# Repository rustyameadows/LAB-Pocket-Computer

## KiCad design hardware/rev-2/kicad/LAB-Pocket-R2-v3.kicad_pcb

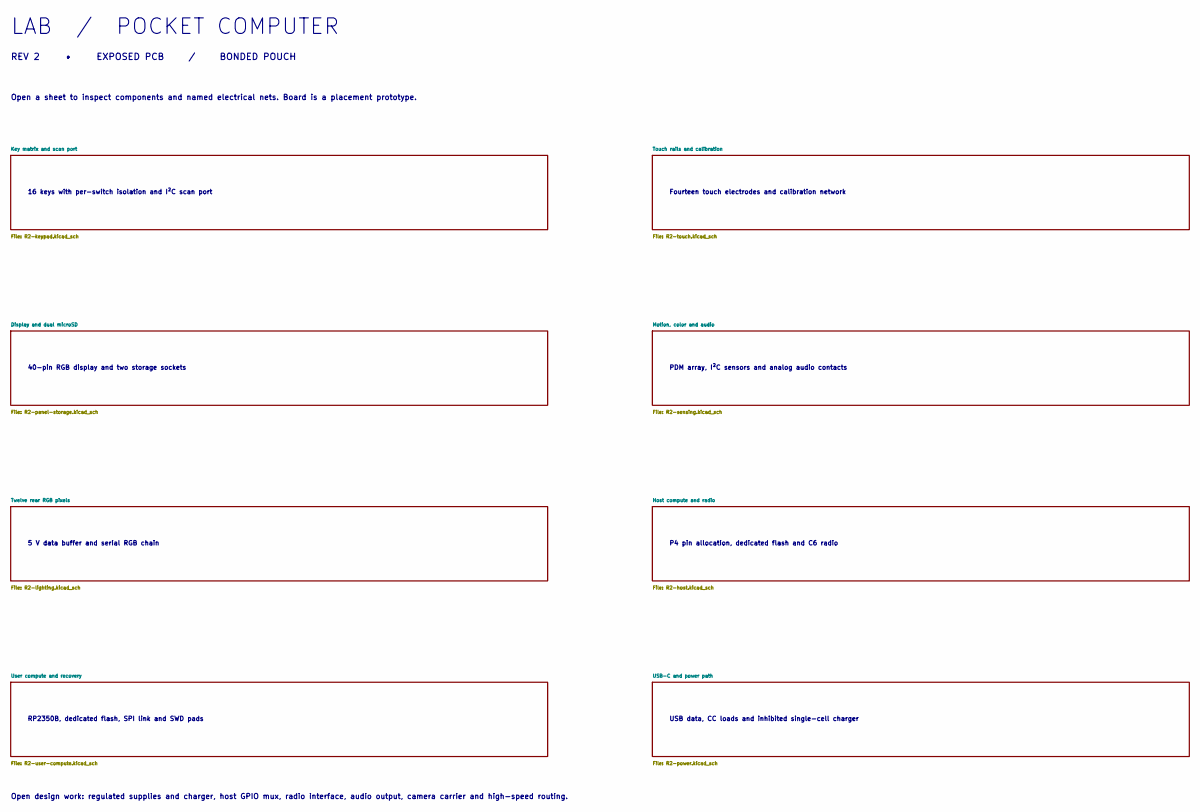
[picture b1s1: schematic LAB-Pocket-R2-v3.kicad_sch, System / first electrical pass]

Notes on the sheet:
LAB / POCKET COMPUTER
REV 2 • EXPOSED PCB / BONDED POUCH
Open a sheet to inspect components and named electrical nets. Board is a placement prototype.
16 keys with per-switch isolation and I²C scan port
Fourteen touch electrodes and calibration network
40-pin RGB display and two storage sockets
PDM array, I²C sensors and analog audio contacts
5 V data buffer and serial RGB chain
P4 pin allocation, dedicated flash and C6 radio
RP2350B, dedicated flash, SPI link and SWD pads
USB data, CC loads and inhibited single-cell charger
Open design work: regulated supplies and charger, host GPIO mux, radio interface, audio output, camera carrier and high-speed routing.

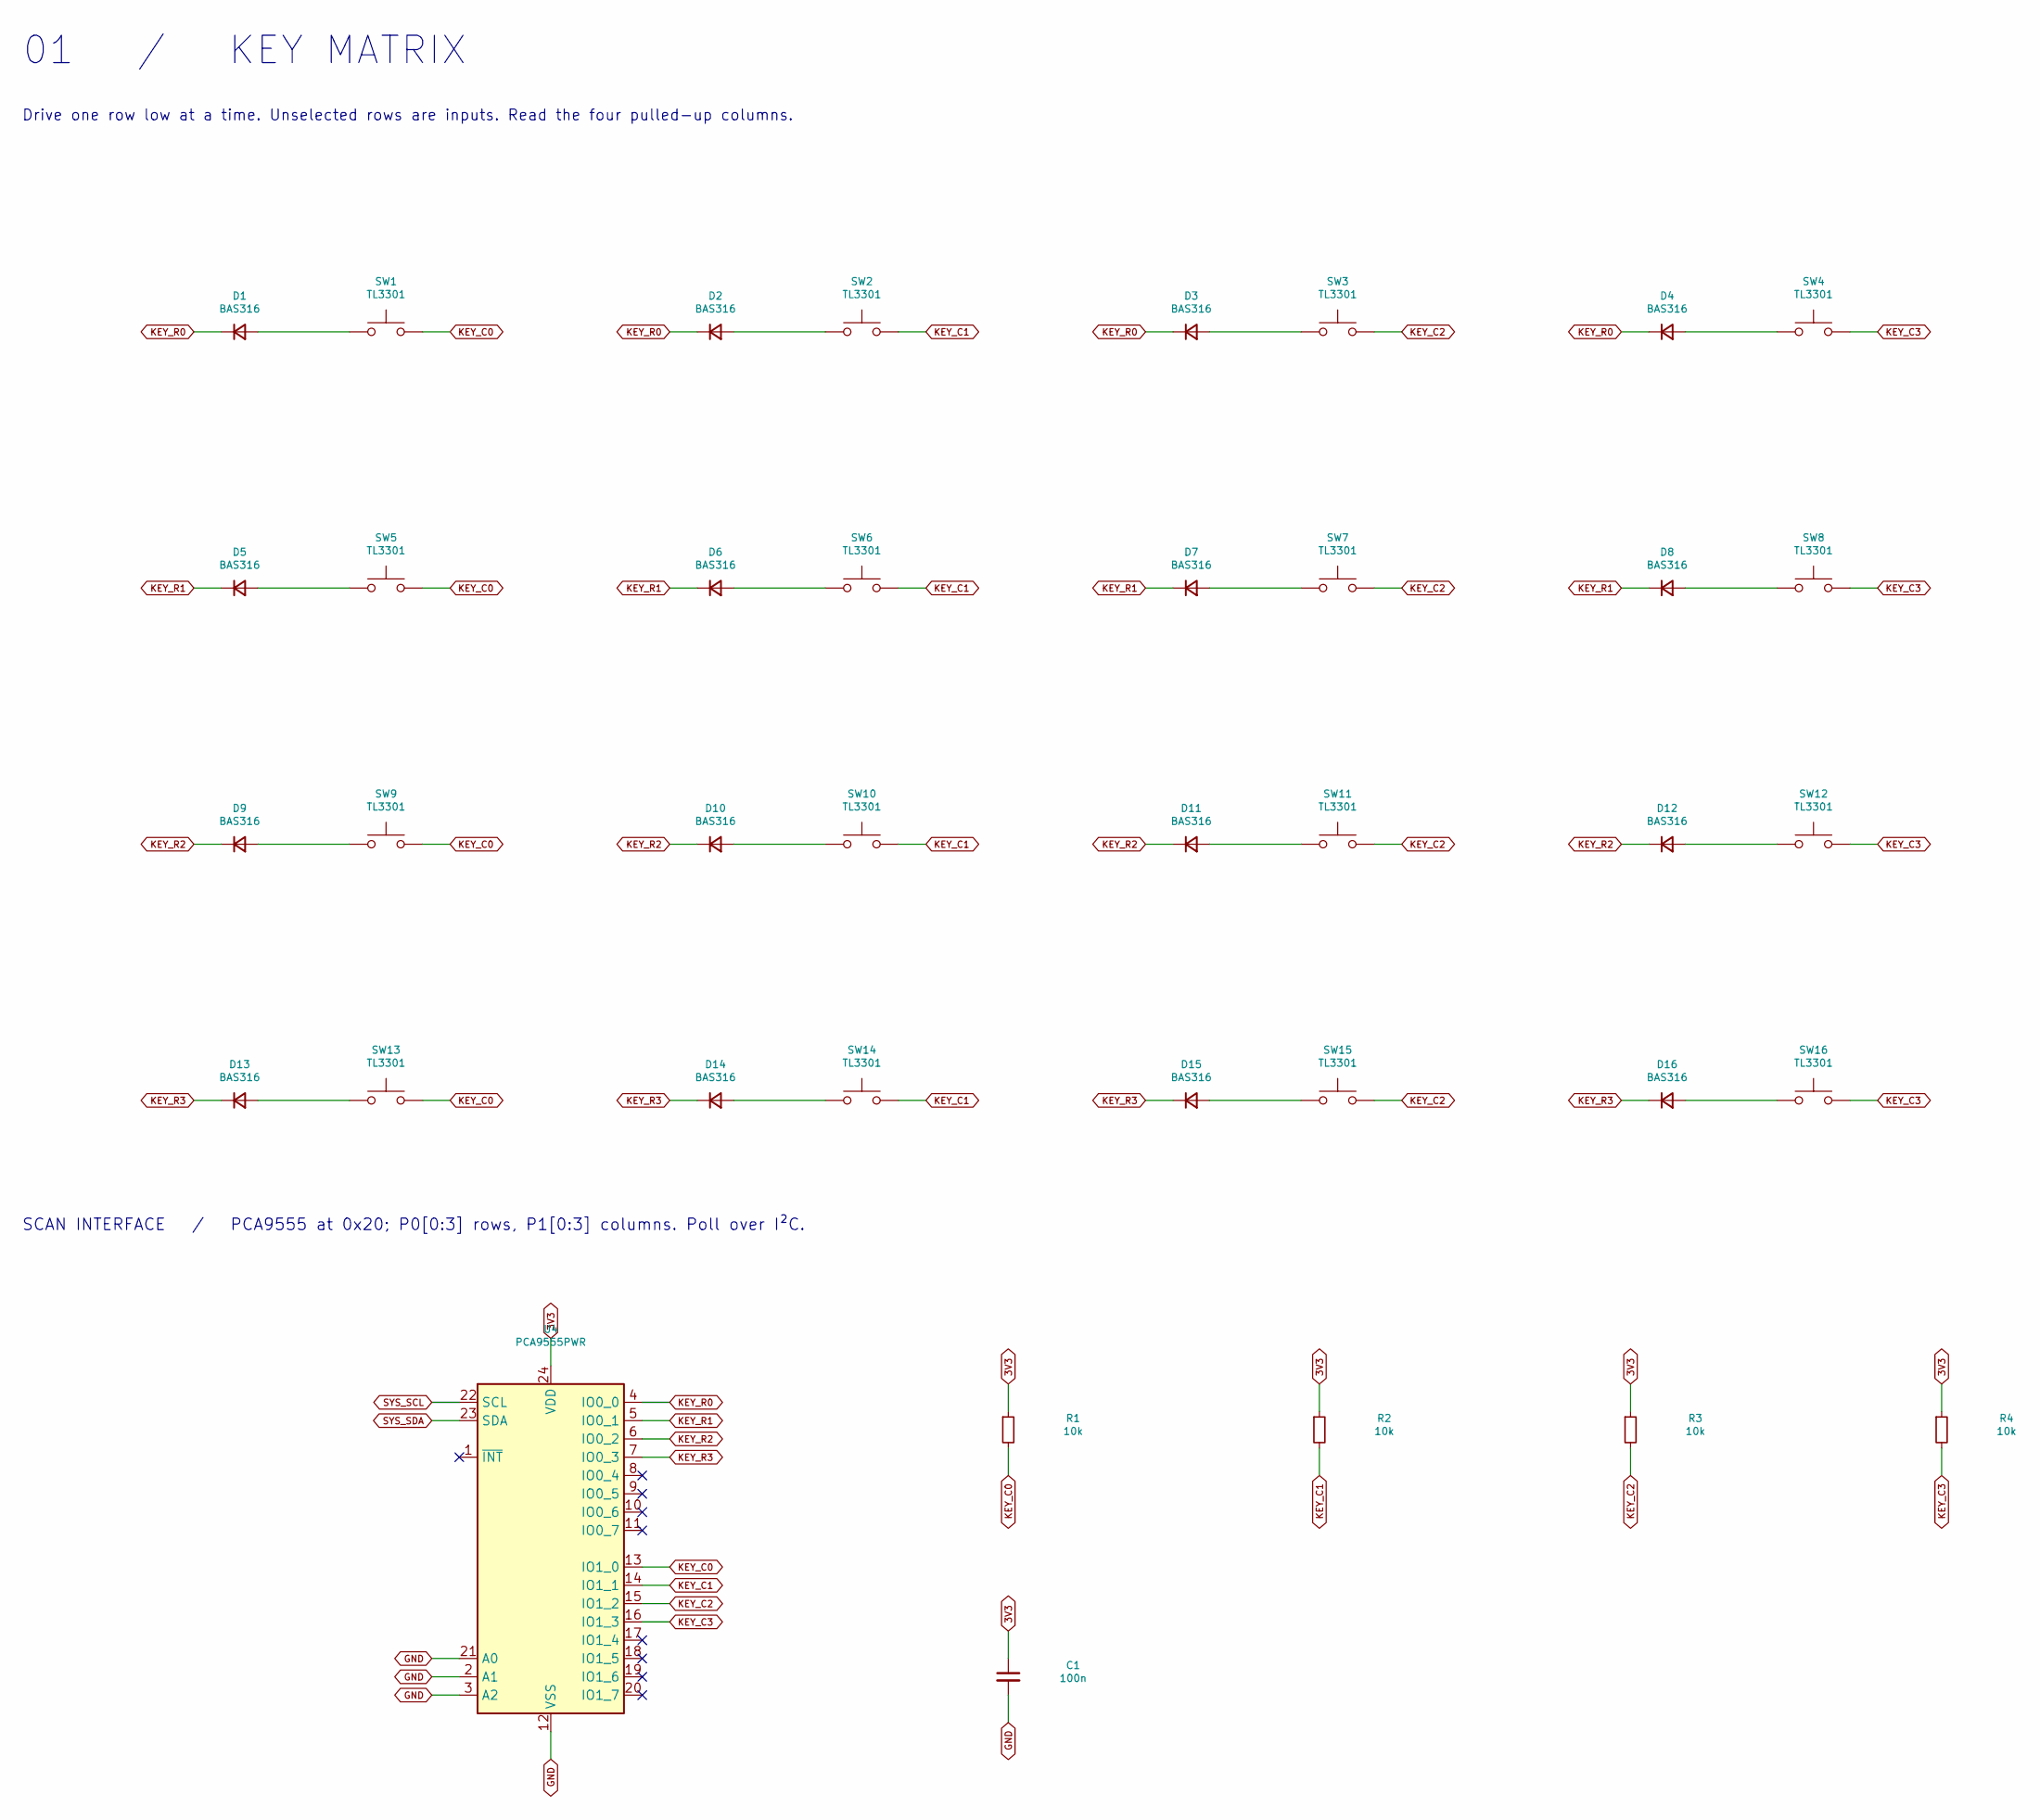
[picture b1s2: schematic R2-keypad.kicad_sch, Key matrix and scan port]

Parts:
C1: 100n; C_0603_1608Metric; MPN C0603C104K5RACTU
D1, D2, D3, D4, D5, D6, D7, D8, D9, D10, D11, D12, D13, D14, D15, D16: BAS316; D_SOD-323; MPN BAS316,115
R1, R2, R3, R4: 10k; R_0603_1608Metric; MPN CRCW060310K0FKEA
SW1, SW2, SW3, SW4, SW5, SW6, SW7, SW8, SW9, SW10, SW11, SW12, SW13, SW14, SW15, SW16: TL3301; SW_Push_1P1T_NO_E-Switch_TL3301NxxxxxG; MPN TL3301NF160QG
U4: PCA9555PWR; TSSOP-24_4.4x7.8mm_P0.65mm; MPN PCA9555PWR

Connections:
3V3: C1.1, R1.1, R2.1, R3.1, R4.1, U4.24 (VDD); also elsewhere on the board
GND: C1.2, U4.2 (A1), U4.3 (A2), U4.12 (VSS), U4.21 (A0); also elsewhere on the board
KEY_C0: R1.2, SW1.2, SW5.2, SW9.2, SW13.2, U4.13 (IO1_0)
KEY_C1: R2.2, SW2.2, SW6.2, SW10.2, SW14.2, U4.14 (IO1_1)
KEY_C2: R3.2, SW3.2, SW7.2, SW11.2, SW15.2, U4.15 (IO1_2)
KEY_C3: R4.2, SW4.2, SW8.2, SW12.2, SW16.2, U4.16 (IO1_3)
KEY_R0: D1.1 (K), D2.1 (K), D3.1 (K), D4.1 (K), U4.4 (IO0_0)
KEY_R1: D5.1 (K), D6.1 (K), D7.1 (K), D8.1 (K), U4.5 (IO0_1)
KEY_R2: D9.1 (K), D10.1 (K), D11.1 (K), D12.1 (K), U4.6 (IO0_2)
KEY_R3: D13.1 (K), D14.1 (K), D15.1 (K), D16.1 (K), U4.7 (IO0_3)
unnamed: D1.2 (A), SW1.1
unnamed: D2.2 (A), SW2.1
unnamed: D3.2 (A), SW3.1
unnamed: D4.2 (A), SW4.1
unnamed: D5.2 (A), SW5.1
unnamed: D6.2 (A), SW6.1
unnamed: D7.2 (A), SW7.1
unnamed: D8.2 (A), SW8.1
unnamed: D9.2 (A), SW9.1
unnamed: D10.2 (A), SW10.1
unnamed: D11.2 (A), SW11.1
unnamed: D12.2 (A), SW12.1
unnamed: D13.2 (A), SW13.1
unnamed: D14.2 (A), SW14.1
unnamed: D15.2 (A), SW15.1
unnamed: D16.2 (A), SW16.1
SYS_SCL: U4.22 (SCL); also elsewhere on the board
SYS_SDA: U4.23 (SDA); also elsewhere on the board

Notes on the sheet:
01 / KEY MATRIX
Drive one row low at a time. Unselected rows are inputs. Read the four pulled-up columns.
SCAN INTERFACE / PCA9555 at 0x20; P0[0:3] rows, P1[0:3] columns. Poll over I²C.

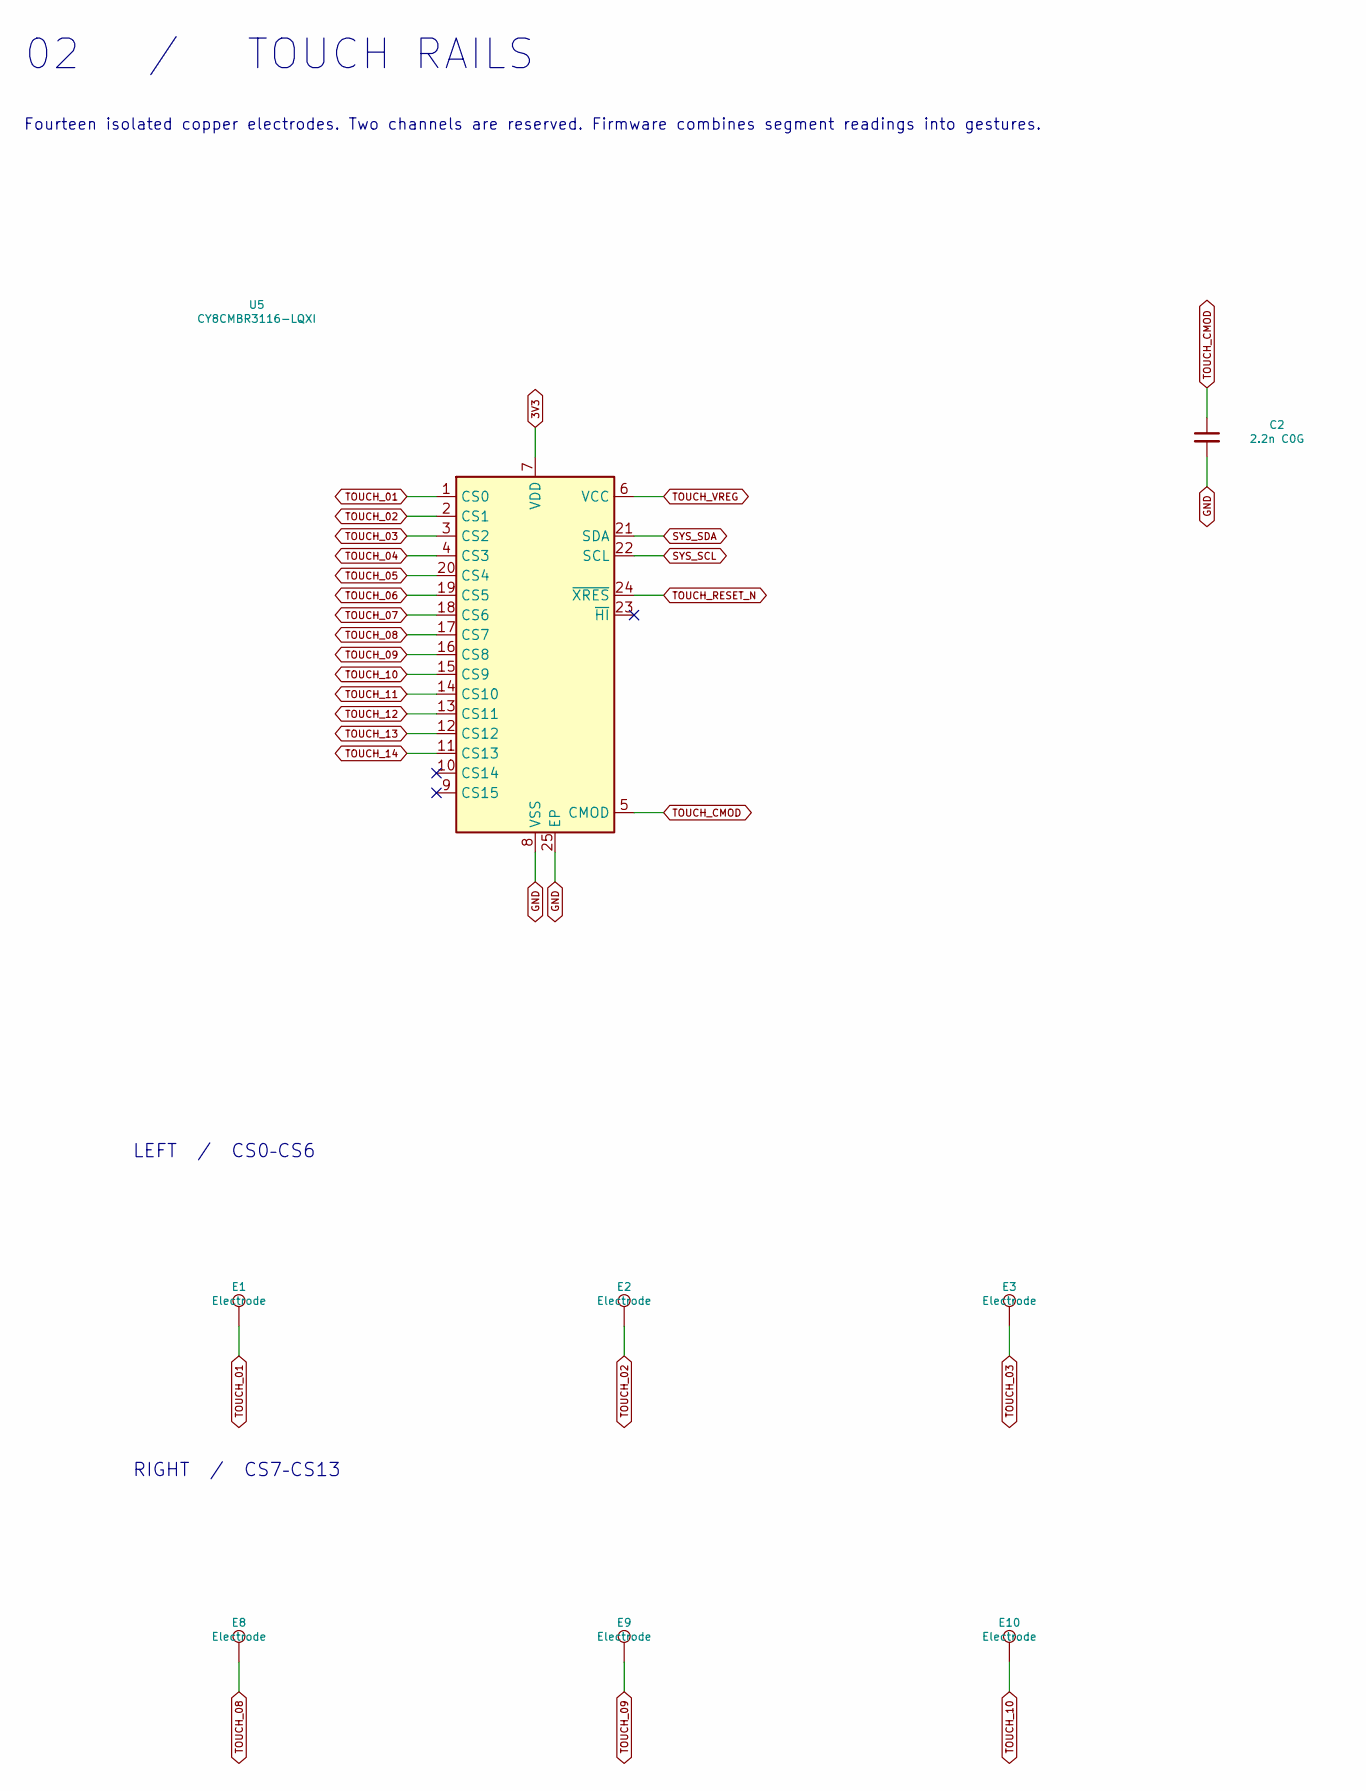
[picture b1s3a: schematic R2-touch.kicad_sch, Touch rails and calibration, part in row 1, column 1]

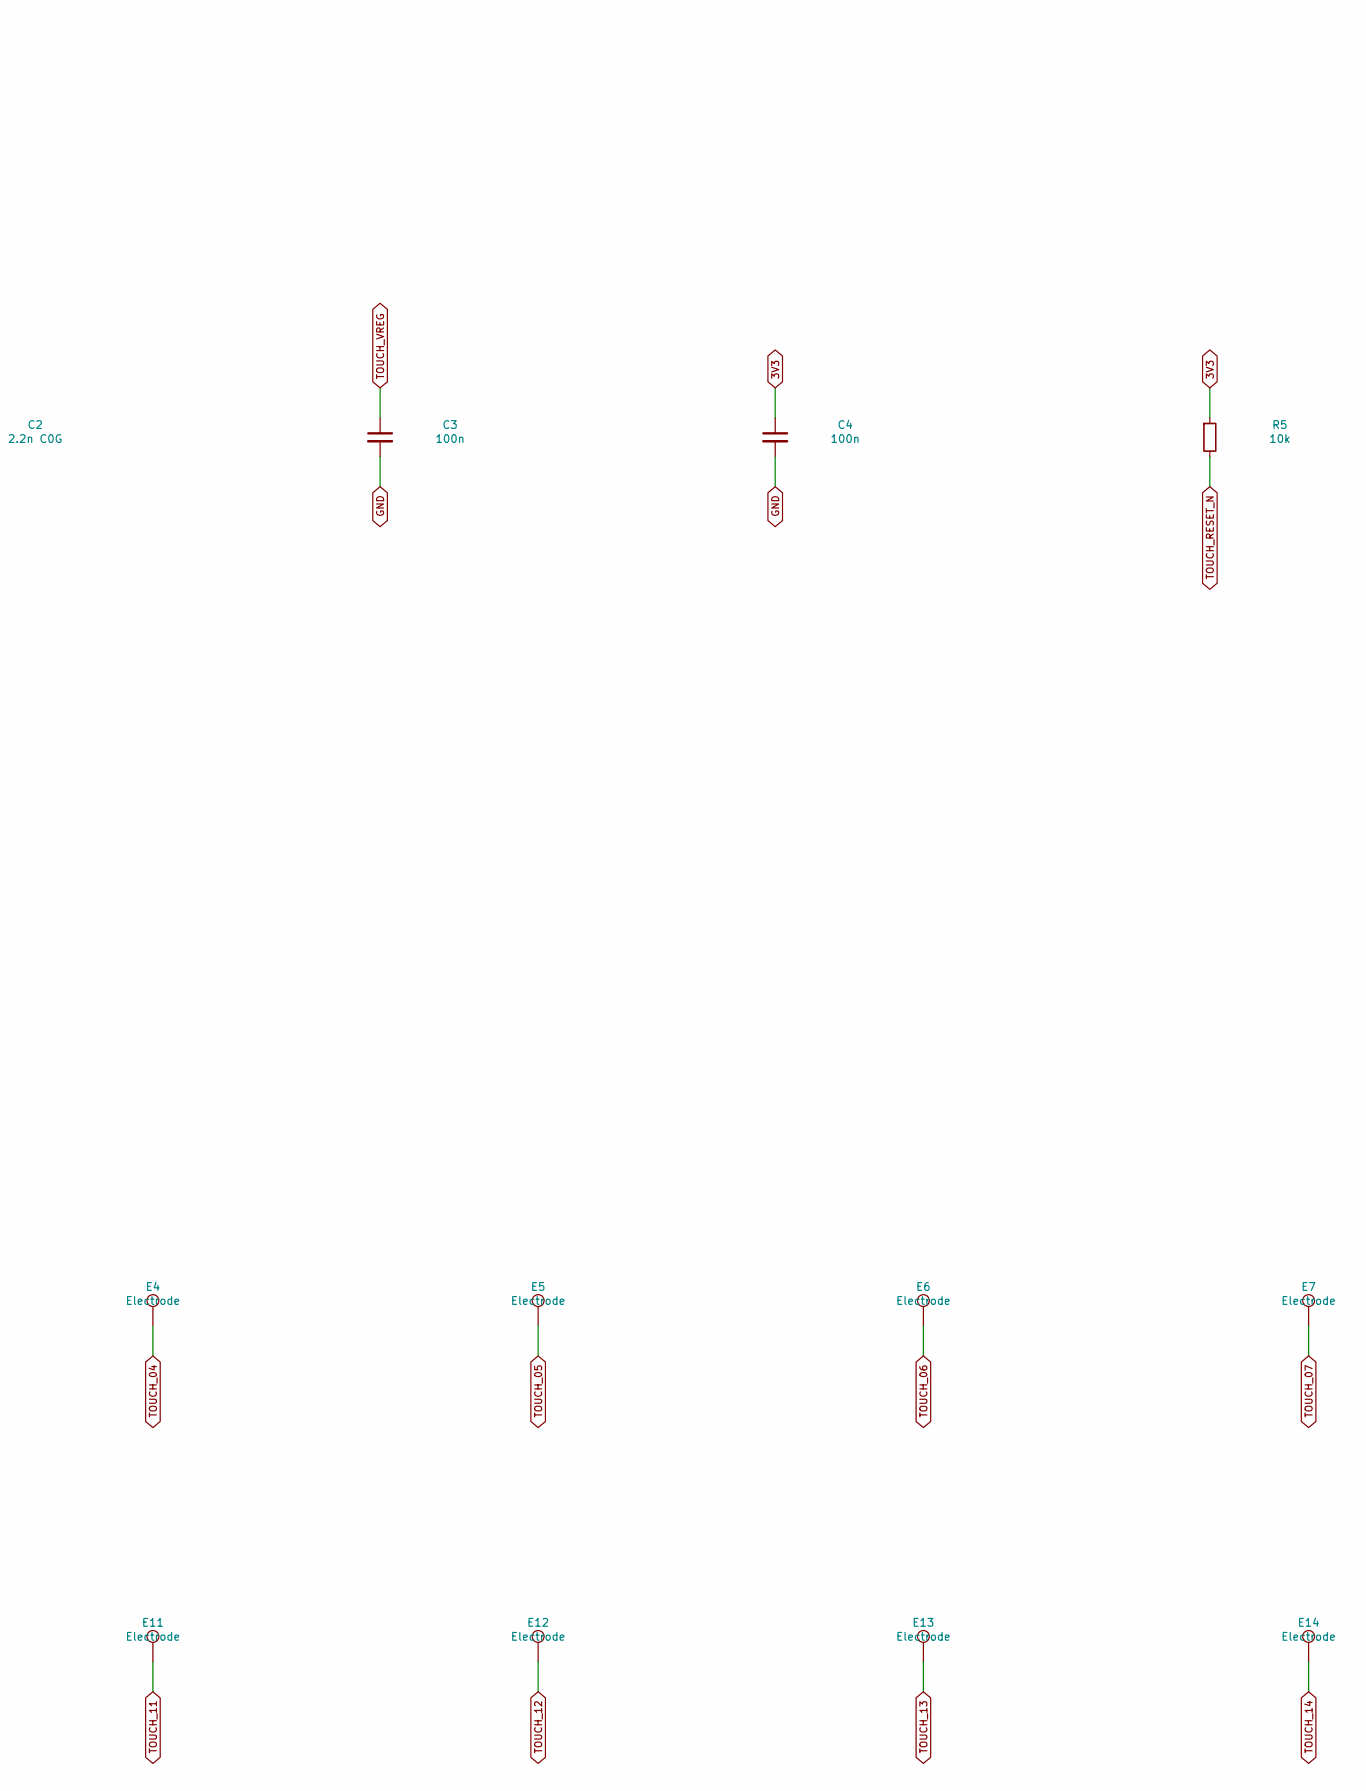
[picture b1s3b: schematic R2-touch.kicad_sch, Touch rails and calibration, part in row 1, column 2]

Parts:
C2: 2.2n C0G; C_0603_1608Metric; MPN C0603C222J5GACTU
C3, C4: 100n; C_0603_1608Metric; MPN C0603C104K5RACTU
E1, E2, E3, E4, E5, E6, E7, E8, E9, E10, E11, E12, E13, E14: Electrode; Touch_7.6x5.0; MPN PCB feature
R5: 10k; R_0603_1608Metric; MPN CRCW060310K0FKEA
U5: CY8CMBR3116-LQXI; QFN-24-1EP_4x4mm_P0.5mm_EP2.6x2.6mm; MPN CY8CMBR3116-LQXI

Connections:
3V3: C4.1, R5.1, U5.7 (VDD); also elsewhere on the board
GND: C2.2, C3.2, C4.2, U5.8 (VSS), U5.25 (EP); also elsewhere on the board
SYS_SCL: U5.22 (SCL); also elsewhere on the board
SYS_SDA: U5.21 (SDA); also elsewhere on the board
TOUCH_01: E1.1, U5.1 (CS0)
TOUCH_02: E2.1, U5.2 (CS1)
TOUCH_03: E3.1, U5.3 (CS2)
TOUCH_04: E4.1, U5.4 (CS3)
TOUCH_05: E5.1, U5.20 (CS4)
TOUCH_06: E6.1, U5.19 (CS5)
TOUCH_07: E7.1, U5.18 (CS6)
TOUCH_08: E8.1, U5.17 (CS7)
TOUCH_09: E9.1, U5.16 (CS8)
TOUCH_10: E10.1, U5.15 (CS9)
TOUCH_11: E11.1, U5.14 (CS10)
TOUCH_12: E12.1, U5.13 (CS11)
TOUCH_13: E13.1, U5.12 (CS12)
TOUCH_14: E14.1, U5.11 (CS13)
TOUCH_CMOD: C2.1, U5.5 (CMOD)
TOUCH_RESET_N: R5.2, U5.24 (~XRES)
TOUCH_VREG: C3.1, U5.6 (VCC)

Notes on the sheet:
02 / TOUCH RAILS
Fourteen isolated copper electrodes. Two channels are reserved. Firmware combines segment readings into gestures.
LEFT / CS0–CS6
RIGHT / CS7–CS13

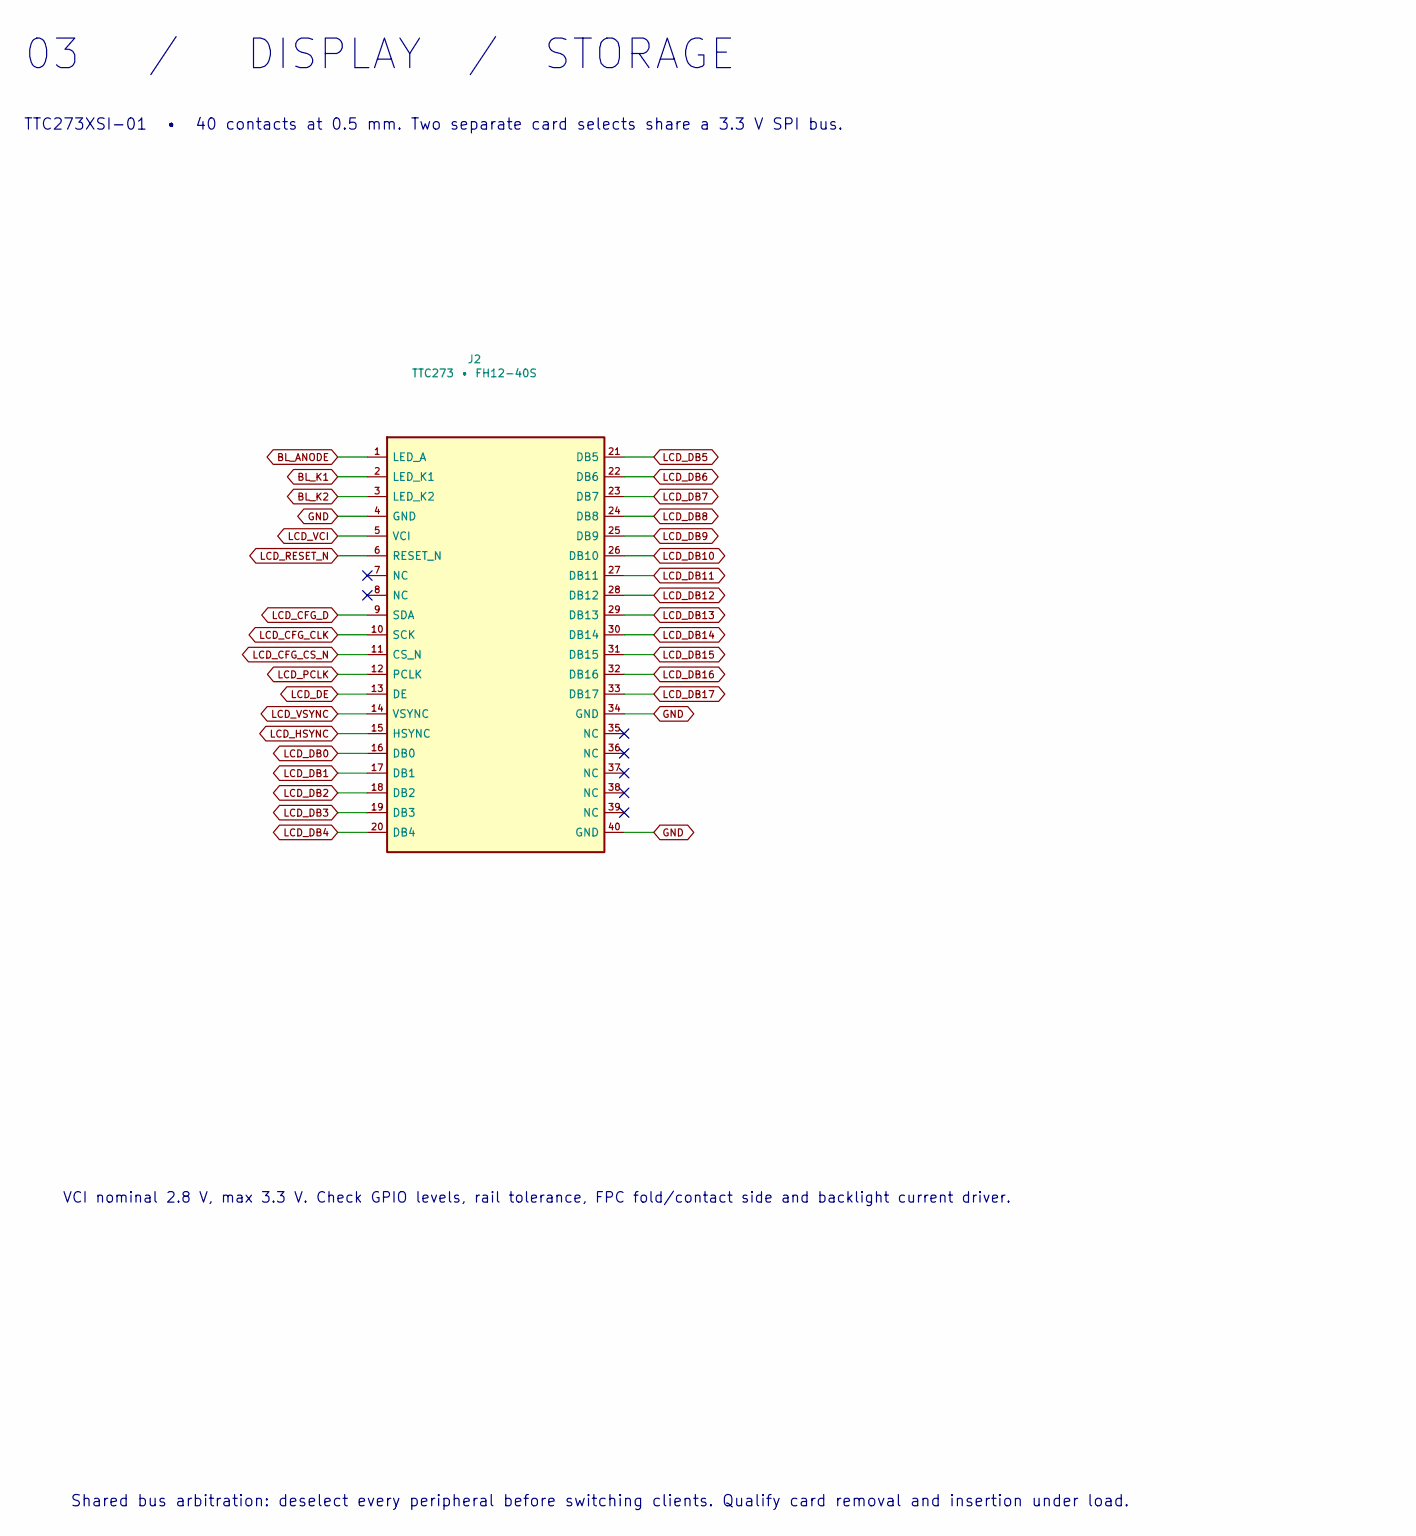
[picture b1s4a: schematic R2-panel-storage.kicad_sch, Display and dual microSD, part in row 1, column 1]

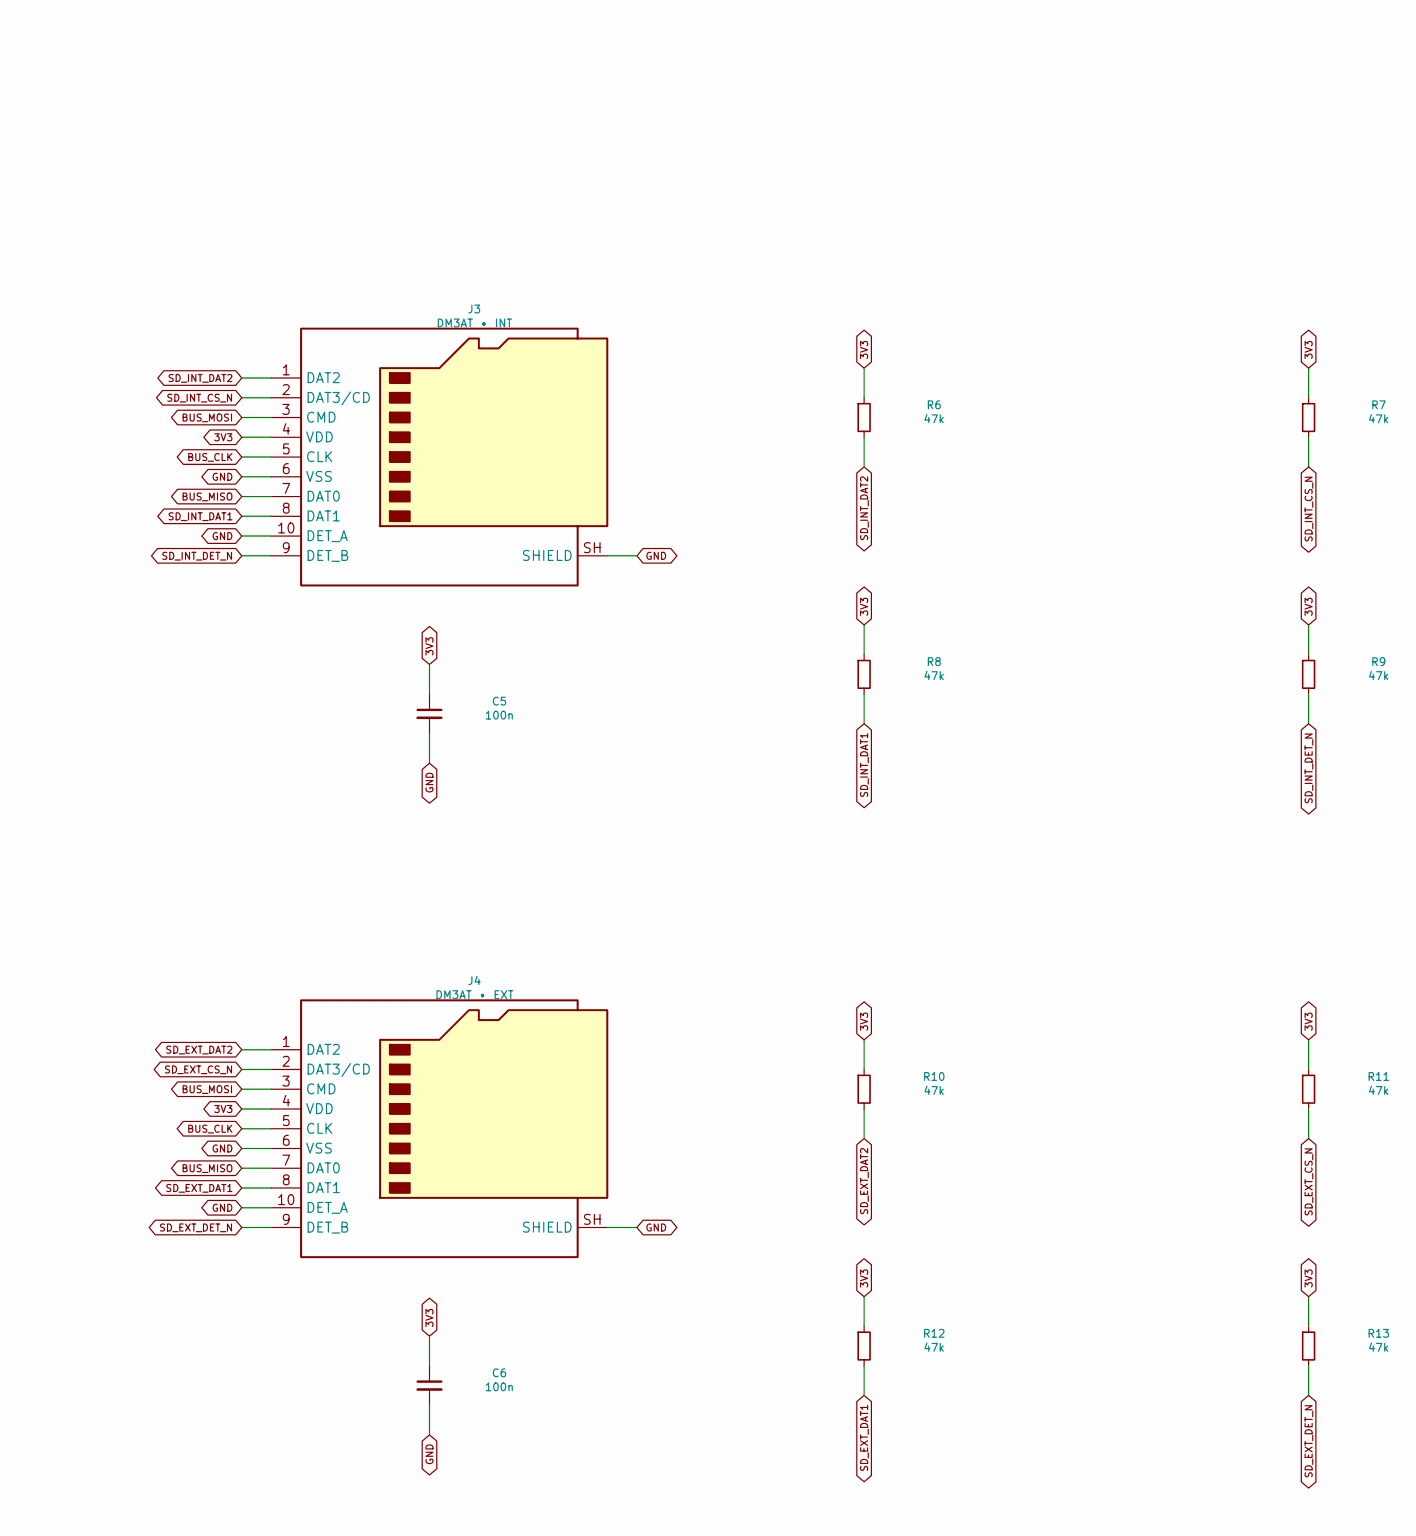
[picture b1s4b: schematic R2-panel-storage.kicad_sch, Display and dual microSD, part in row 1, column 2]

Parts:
C5, C6: 100n; C_0603_1608Metric; MPN C0603C104K5RACTU
J2: TTC273 • FH12-40S; Hirose_FH12-40S-0.5SH_1x40-1MP_P0.50mm_Horizontal; MPN FH12-40S-0.5SH(55)
J3: DM3AT • INT; microSD_HC_Hirose_DM3AT-SF-PEJM5; MPN DM3AT-SF-PEJM5
J4: DM3AT • EXT; microSD_HC_Hirose_DM3AT-SF-PEJM5; MPN DM3AT-SF-PEJM5
R6, R7, R8, R9, R10, R11, R12, R13: 47k; R_0603_1608Metric; MPN CRCW060347K0FKEA

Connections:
3V3: C5.1, C6.1, J3.4 (VDD), J4.4 (VDD), R6.1, R7.1, R8.1, R9.1, R10.1, R11.1, R12.1, R13.1; also elsewhere on the board
BL_ANODE: J2.1 (LED_A)
BL_K1: J2.2 (LED_K1)
BL_K2: J2.3 (LED_K2)
BUS_CLK: J3.5 (CLK), J4.5 (CLK); also elsewhere on the board
BUS_MISO: J3.7 (DAT0), J4.7 (DAT0); also elsewhere on the board
BUS_MOSI: J3.3 (CMD), J4.3 (CMD); also elsewhere on the board
GND: C5.2, C6.2, J2.4 (GND), J2.34 (GND), J2.40 (GND), J3.6 (VSS), J3.10 (DET_A), J3.SH (SHIELD), J4.6 (VSS), J4.10 (DET_A), J4.SH (SHIELD); also elsewhere on the board
LCD_CFG_CLK: J2.10 (SCK); also elsewhere on the board
LCD_CFG_CS_N: J2.11 (CS_N); also elsewhere on the board
LCD_CFG_D: J2.9 (SDA); also elsewhere on the board
LCD_DB0: J2.16 (DB0); also elsewhere on the board
LCD_DB1: J2.17 (DB1); also elsewhere on the board
LCD_DB2: J2.18 (DB2); also elsewhere on the board
LCD_DB3: J2.19 (DB3); also elsewhere on the board
LCD_DB4: J2.20 (DB4); also elsewhere on the board
LCD_DB5: J2.21 (DB5); also elsewhere on the board
LCD_DB6: J2.22 (DB6); also elsewhere on the board
LCD_DB7: J2.23 (DB7); also elsewhere on the board
LCD_DB8: J2.24 (DB8); also elsewhere on the board
LCD_DB9: J2.25 (DB9); also elsewhere on the board
LCD_DB10: J2.26 (DB10); also elsewhere on the board
LCD_DB11: J2.27 (DB11); also elsewhere on the board
LCD_DB12: J2.28 (DB12); also elsewhere on the board
LCD_DB13: J2.29 (DB13); also elsewhere on the board
LCD_DB14: J2.30 (DB14); also elsewhere on the board
LCD_DB15: J2.31 (DB15); also elsewhere on the board
LCD_DB16: J2.32 (DB16); also elsewhere on the board
LCD_DB17: J2.33 (DB17); also elsewhere on the board
LCD_DE: J2.13 (DE); also elsewhere on the board
LCD_HSYNC: J2.15 (HSYNC); also elsewhere on the board
LCD_PCLK: J2.12 (PCLK); also elsewhere on the board
LCD_RESET_N: J2.6 (RESET_N); also elsewhere on the board
LCD_VCI: J2.5 (VCI)
LCD_VSYNC: J2.14 (VSYNC); also elsewhere on the board
SD_EXT_CS_N: J4.2 (DAT3/CD), R11.2; also elsewhere on the board
SD_EXT_DAT1: J4.8 (DAT1), R12.2
SD_EXT_DAT2: J4.1 (DAT2), R10.2
SD_EXT_DET_N: J4.9 (DET_B), R13.2; also elsewhere on the board
SD_INT_CS_N: J3.2 (DAT3/CD), R7.2; also elsewhere on the board
SD_INT_DAT1: J3.8 (DAT1), R8.2
SD_INT_DAT2: J3.1 (DAT2), R6.2
SD_INT_DET_N: J3.9 (DET_B), R9.2; also elsewhere on the board

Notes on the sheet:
03 / DISPLAY / STORAGE
TTC273XSI-01 • 40 contacts at 0.5 mm. Two separate card selects share a 3.3 V SPI bus.
VCI nominal 2.8 V, max 3.3 V. Check GPIO levels, rail tolerance, FPC fold/contact side and backlight current driver.
Shared bus arbitration: deselect every peripheral before switching clients. Qualify card removal and insertion under load.
